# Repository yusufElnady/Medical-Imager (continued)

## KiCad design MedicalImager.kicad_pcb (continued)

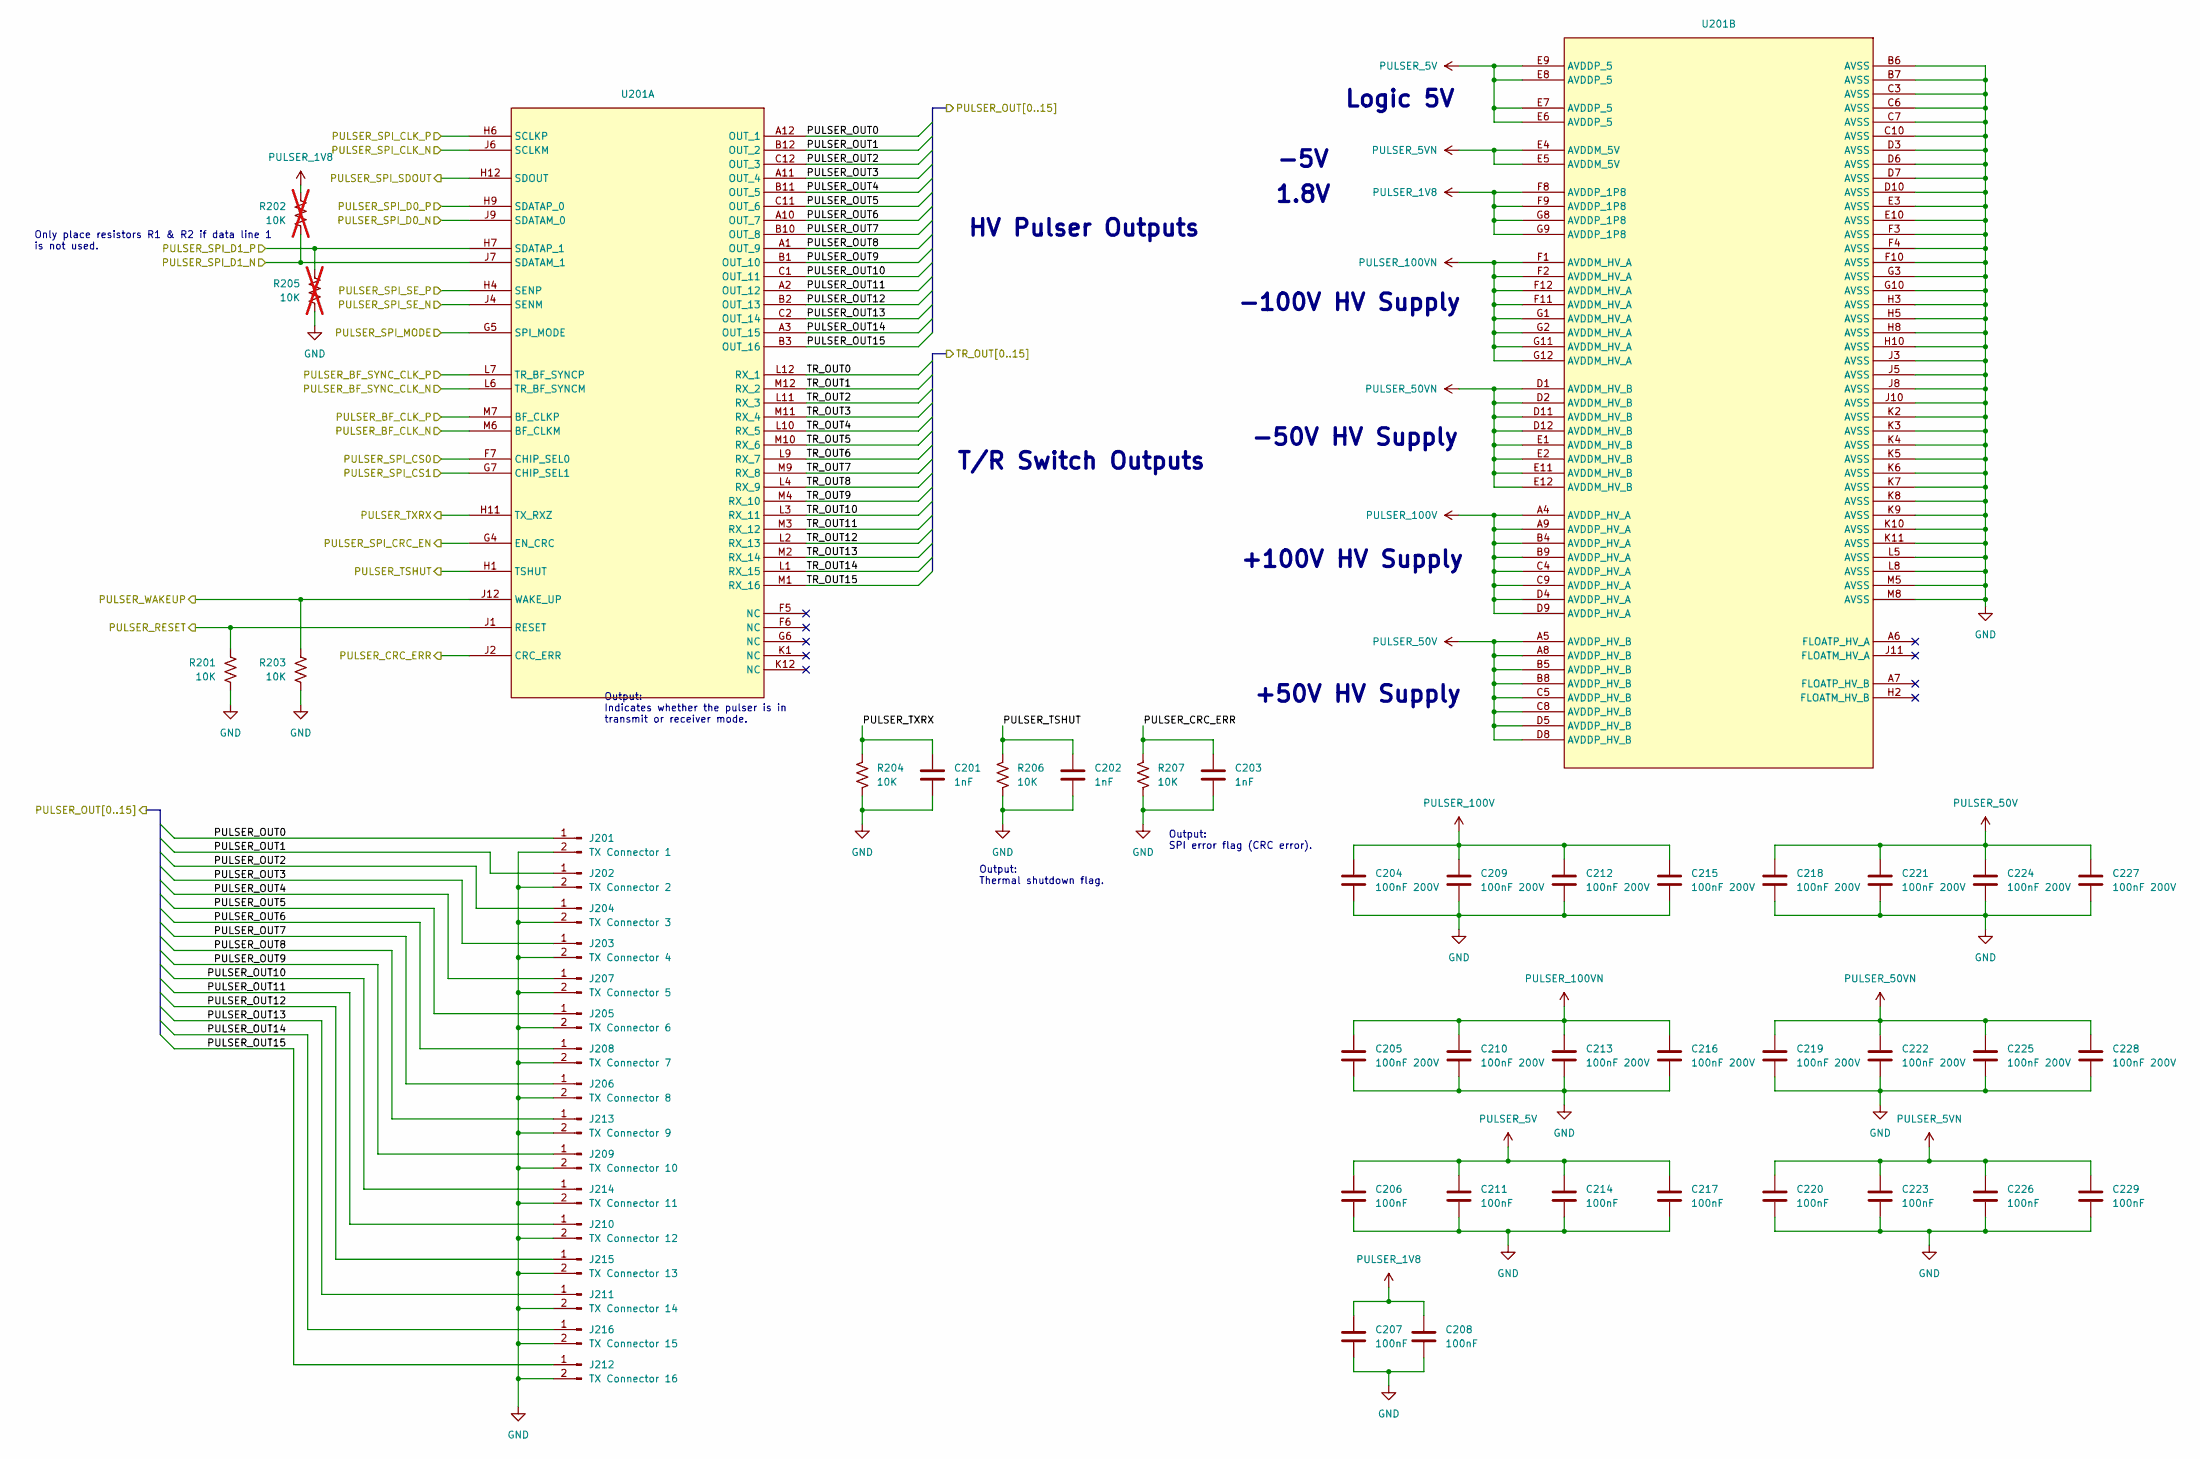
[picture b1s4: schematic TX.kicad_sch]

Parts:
C201, C202, C203: 1nF; C_0402_1005Metric
C204, C205, C209, C210, C212, C213, C215, C216, C218, C219, C221, C222, C224, C225, C227, C228: 100nF 200V; C_0805_2012Metric
C206, C207, C208, C211, C214, C217, C220, C223, C226, C229: 100nF; C_0402_1005Metric
J201: TX Connector 1; PinHeader_1x02_P2.54mm_Vertical
J202: TX Connector 2; PinHeader_1x02_P2.54mm_Vertical
J203: TX Connector 4; PinHeader_1x02_P2.54mm_Vertical
J204: TX Connector 3; PinHeader_1x02_P2.54mm_Vertical
J205: TX Connector 6; PinHeader_1x02_P2.54mm_Vertical
J206: TX Connector 8; PinHeader_1x02_P2.54mm_Vertical
J207: TX Connector 5; PinHeader_1x02_P2.54mm_Vertical
J208: TX Connector 7; PinHeader_1x02_P2.54mm_Vertical
J209: TX Connector 10; PinHeader_1x02_P2.54mm_Vertical
J210: TX Connector 12; PinHeader_1x02_P2.54mm_Vertical
J211: TX Connector 14; PinHeader_1x02_P2.54mm_Vertical
J212: TX Connector 16; PinHeader_1x02_P2.54mm_Vertical
J213: TX Connector 9; PinHeader_1x02_P2.54mm_Vertical
J214: TX Connector 11; PinHeader_1x02_P2.54mm_Vertical
J215: TX Connector 13; PinHeader_1x02_P2.54mm_Vertical
J216: TX Connector 15; PinHeader_1x02_P2.54mm_Vertical
R201, R203, R204, R206, R207: 10K; R_0402_1005Metric
R202, R205: 10K; R_0402_1005Metric; not fitted
U201: BGA-144_10.0x10.0mm_Layout12x12_P0.8mm_TI-ALH0144A

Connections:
/RX/TR_OUT0: U201.L12 (RX_1); also elsewhere on the board
/RX/TR_OUT1: U201.M12 (RX_2); also elsewhere on the board
/RX/TR_OUT2: U201.L11 (RX_3); also elsewhere on the board
/RX/TR_OUT3: U201.M11 (RX_4); also elsewhere on the board
/RX/TR_OUT4: U201.L10 (RX_5); also elsewhere on the board
/RX/TR_OUT5: U201.M10 (RX_6); also elsewhere on the board
/RX/TR_OUT6: U201.L9 (RX_7); also elsewhere on the board
/RX/TR_OUT7: U201.M9 (RX_8); also elsewhere on the board
/RX/TR_OUT8: U201.L4 (RX_9); also elsewhere on the board
/RX/TR_OUT9: U201.M4 (RX_10); also elsewhere on the board
/RX/TR_OUT10: U201.L3 (RX_11); also elsewhere on the board
/RX/TR_OUT11: U201.M3 (RX_12); also elsewhere on the board
/RX/TR_OUT12: U201.L2 (RX_13); also elsewhere on the board
/RX/TR_OUT13: U201.M2 (RX_14); also elsewhere on the board
/RX/TR_OUT14: U201.L1 (RX_15); also elsewhere on the board
/RX/TR_OUT15: U201.M1 (RX_16); also elsewhere on the board
/RX/TX_BF_CLK_N: U201.M6 (BF_CLKM); also elsewhere on the board
/RX/TX_BF_CLK_P: U201.M7 (BF_CLKP); also elsewhere on the board
/SOM/PULSER_BF_SYNC_CLK_N: U201.L6 (TR_BF_SYNCM); also elsewhere on the board
/SOM/PULSER_BF_SYNC_CLK_P: U201.L7 (TR_BF_SYNCP); also elsewhere on the board
/SOM/PULSER_RESET: R201.1, U201.J1 (RESET); also elsewhere on the board
/SOM/PULSER_SPI_CLK_N: U201.J6 (SCLKM); also elsewhere on the board
/SOM/PULSER_SPI_CLK_P: U201.H6 (SCLKP); also elsewhere on the board
/SOM/PULSER_SPI_CRC_EN: U201.G4 (EN_CRC); also elsewhere on the board
/SOM/PULSER_SPI_CS0: U201.F7 (CHIP_SEL0); also elsewhere on the board
/SOM/PULSER_SPI_CS1: U201.G7 (CHIP_SEL1); also elsewhere on the board
/SOM/PULSER_SPI_D0_N: U201.J9 (SDATAM_0); also elsewhere on the board
/SOM/PULSER_SPI_D0_P: U201.H9 (SDATAP_0); also elsewhere on the board
/SOM/PULSER_SPI_D1_N: R202.2, U201.J7 (SDATAM_1); also elsewhere on the board
/SOM/PULSER_SPI_D1_P: R205.1, U201.H7 (SDATAP_1); also elsewhere on the board
/SOM/PULSER_SPI_MODE: U201.G5 (SPI_MODE); also elsewhere on the board
/SOM/PULSER_SPI_SDOUT: U201.H12 (SDOUT); also elsewhere on the board
/SOM/PULSER_SPI_SE_N: U201.J4 (SENM); also elsewhere on the board
/SOM/PULSER_SPI_SE_P: U201.H4 (SENP); also elsewhere on the board
/SOM/PULSER_WAKEUP: R203.1, U201.J12 (WAKE_UP); also elsewhere on the board
/TX/PULSER_CRC_ERR: C203.1, R207.1, U201.J2 (CRC_ERR); also elsewhere on the board
/TX/PULSER_OUT0: J201.1, U201.A12 (OUT_1)
/TX/PULSER_OUT1: J202.1, U201.B12 (OUT_2)
/TX/PULSER_OUT2: J204.1, U201.C12 (OUT_3)
/TX/PULSER_OUT3: J203.1, U201.A11 (OUT_4)
/TX/PULSER_OUT4: J207.1, U201.B11 (OUT_5)
/TX/PULSER_OUT5: J205.1, U201.C11 (OUT_6)
/TX/PULSER_OUT6: J208.1, U201.A10 (OUT_7)
/TX/PULSER_OUT7: J206.1, U201.B10 (OUT_8)
/TX/PULSER_OUT8: J213.1, U201.A1 (OUT_9)
/TX/PULSER_OUT9: J209.1, U201.B1 (OUT_10)
/TX/PULSER_OUT10: J214.1, U201.C1 (OUT_11)
/TX/PULSER_OUT11: J210.1, U201.A2 (OUT_12)
/TX/PULSER_OUT12: J215.1, U201.B2 (OUT_13)
/TX/PULSER_OUT13: J211.1, U201.C2 (OUT_14)
/TX/PULSER_OUT14: J216.1, U201.A3 (OUT_15)
/TX/PULSER_OUT15: J212.1, U201.B3 (OUT_16)
/TX/PULSER_TSHUT: C202.1, R206.1, U201.H1 (TSHUT); also elsewhere on the board
/TX/PULSER_TXRX: C201.1, R204.1, U201.H11 (TX_RXZ); also elsewhere on the board
GND: C201.2, C202.2, C203.2, C204.2, C205.2, C206.2, C207.2, C208.2, C209.2, C210.2, C211.2, C212.2, C213.2, C214.2, C215.2, C216.2, C217.2, C218.2, C219.2, C220.2, C221.2, C222.2, C223.2, C224.2, C225.2, C226.2, C227.2, C228.2, C229.2, J201.2, J202.2, J203.2, J204.2, J205.2, J206.2, J207.2, J208.2, J209.2, J210.2, J211.2, J212.2, J213.2, J214.2, J215.2, J216.2, R201.2, R203.2, R204.2, R205.2, R206.2, R207.2, U201.B6 (AVSS), U201.B7 (AVSS), U201.C3 (AVSS), U201.C6 (AVSS), U201.C7 (AVSS), U201.C10 (AVSS), U201.D3 (AVSS), U201.D6 (AVSS), U201.D7 (AVSS), U201.D10 (AVSS), U201.E3 (AVSS), U201.E10 (AVSS), U201.F3 (AVSS), U201.F4 (AVSS), U201.F10 (AVSS), U201.G3 (AVSS), U201.G10 (AVSS), U201.H3 (AVSS), U201.H5 (AVSS), U201.H8 (AVSS), U201.H10 (AVSS), U201.J3 (AVSS), U201.J5 (AVSS), U201.J8 (AVSS), U201.J10 (AVSS), U201.K2 (AVSS), U201.K3 (AVSS), U201.K4 (AVSS), U201.K5 (AVSS), U201.K6 (AVSS), U201.K7 (AVSS), U201.K8 (AVSS), U201.K9 (AVSS), U201.K10 (AVSS), U201.K11 (AVSS), U201.L5 (AVSS), U201.L8 (AVSS), U201.M5 (AVSS), U201.M8 (AVSS); also elsewhere on the board
IM_5V: C206.1, C211.1, C214.1, C217.1, U201.E6 (AVDDP_5), U201.E7 (AVDDP_5), U201.E8 (AVDDP_5), U201.E9 (AVDDP_5); also elsewhere on the board
PULSER_1V8: C207.1, C208.1, R202.1, U201.F8 (AVDDP_1P8), U201.F9 (AVDDP_1P8), U201.G8 (AVDDP_1P8), U201.G9 (AVDDP_1P8); also elsewhere on the board
PULSER_5VN: C220.1, C223.1, C226.1, C229.1, U201.E4 (AVDDM_5V), U201.E5 (AVDDM_5V); also elsewhere on the board
PULSER_50V: C218.1, C221.1, C224.1, C227.1, U201.A5 (AVDDP_HV_B), U201.A8 (AVDDP_HV_B), U201.B5 (AVDDP_HV_B), U201.B8 (AVDDP_HV_B), U201.C5 (AVDDP_HV_B), U201.C8 (AVDDP_HV_B), U201.D5 (AVDDP_HV_B), U201.D8 (AVDDP_HV_B); also elsewhere on the board
PULSER_50VN: C219.1, C222.1, C225.1, C228.1, U201.D1 (AVDDM_HV_B), U201.D2 (AVDDM_HV_B), U201.D11 (AVDDM_HV_B), U201.D12 (AVDDM_HV_B), U201.E1 (AVDDM_HV_B), U201.E2 (AVDDM_HV_B), U201.E11 (AVDDM_HV_B), U201.E12 (AVDDM_HV_B); also elsewhere on the board
PULSER_100V: C204.1, C209.1, C212.1, C215.1, U201.A4 (AVDDP_HV_A), U201.A9 (AVDDP_HV_A), U201.B4 (AVDDP_HV_A), U201.B9 (AVDDP_HV_A), U201.C4 (AVDDP_HV_A), U201.C9 (AVDDP_HV_A), U201.D4 (AVDDP_HV_A), U201.D9 (AVDDP_HV_A); also elsewhere on the board
PULSER_100VN: C205.1, C210.1, C213.1, C216.1, U201.F1 (AVDDM_HV_A), U201.F2 (AVDDM_HV_A), U201.F11 (AVDDM_HV_A), U201.F12 (AVDDM_HV_A), U201.G1 (AVDDM_HV_A), U201.G2 (AVDDM_HV_A), U201.G11 (AVDDM_HV_A), U201.G12 (AVDDM_HV_A); also elsewhere on the board

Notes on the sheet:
-50V HV Supply
-5V
1.8V
+100V HV Supply
Logic 5V
HV Pulser Outputs
Only place resistors R1 & R2 if data line 1 is not used.
Output: Indicates whether the pulser is in transmit or receiver mode.
Output: SPI error flag (CRC error).
-100V HV Supply
+50V HV Supply
Output: Thermal shutdown flag.
T/R Switch Outputs

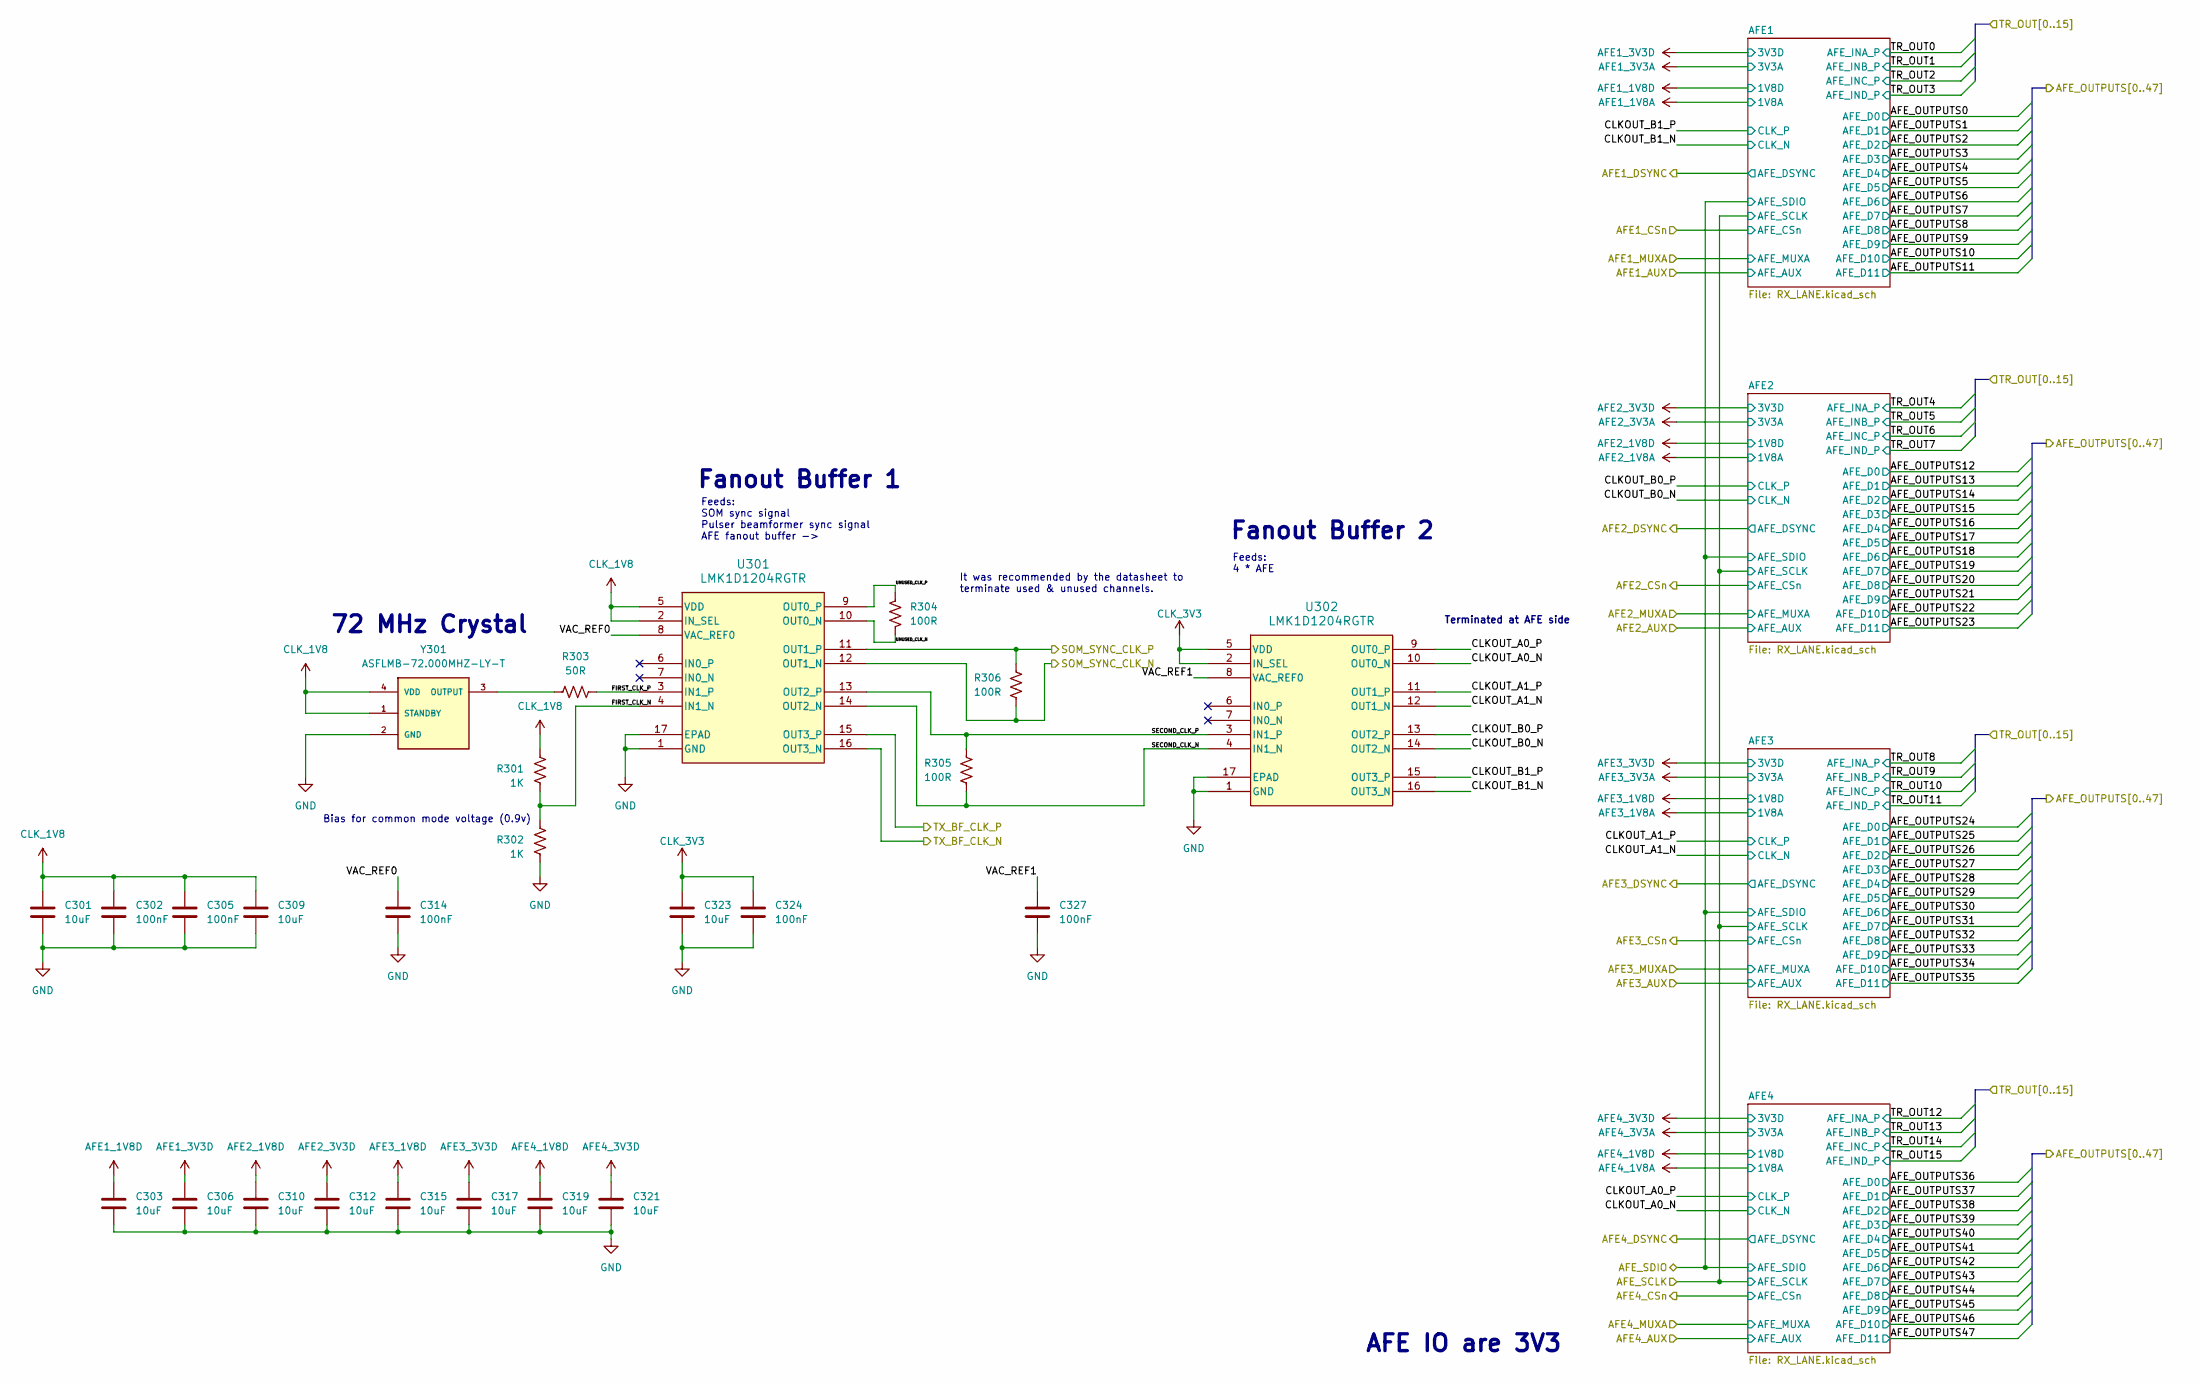
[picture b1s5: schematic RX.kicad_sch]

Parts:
C301, C303, C306, C309, C310, C312, C315, C317, C319, C321, C323: 10uF; C_0402_1005Metric
C302, C305, C314, C324, C327: 100nF; C_0402_1005Metric
R301, R302: 1K; R_0402_1005Metric
R303: 50R; R_0402_1005Metric
R304, R305, R306: 100R; R_0402_1005Metric
U301, U302: LMK1D1204RGTR; VQFN16_RGT_TEX
Y301: ASFLMB-72.000MHZ-LY-T; XTAL_ASFLMB-72.000MHZ-LY-T; PARTREV 1.4.2021

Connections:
/RX/CLKOUT_A0_N: U302.10 (OUT0_N); also elsewhere on the board
/RX/CLKOUT_A0_P: U302.9 (OUT0_P); also elsewhere on the board
/RX/CLKOUT_A1_N: U302.12 (OUT1_N); also elsewhere on the board
/RX/CLKOUT_A1_P: U302.11 (OUT1_P); also elsewhere on the board
/RX/CLKOUT_B0_N: U302.14 (OUT2_N); also elsewhere on the board
/RX/CLKOUT_B0_P: U302.13 (OUT2_P); also elsewhere on the board
/RX/CLKOUT_B1_N: U302.16 (OUT3_N); also elsewhere on the board
/RX/CLKOUT_B1_P: U302.15 (OUT3_P); also elsewhere on the board
/RX/FIRST_CLK_N: R301.2, R302.1, U301.4 (IN1_N)
/RX/FIRST_CLK_P: R303.1, U301.3 (IN1_P)
/RX/SECOND_CLK_N: R305.2, U301.14 (OUT2_N), U302.4 (IN1_N)
/RX/SECOND_CLK_P: R305.1, U301.13 (OUT2_P), U302.3 (IN1_P)
/RX/SOM_SYNC_CLK_N: R306.2, U301.12 (OUT1_N); also elsewhere on the board
/RX/SOM_SYNC_CLK_P: R306.1, U301.11 (OUT1_P); also elsewhere on the board
/RX/TX_BF_CLK_N: U301.16 (OUT3_N); also elsewhere on the board
/RX/TX_BF_CLK_P: U301.15 (OUT3_P); also elsewhere on the board
/RX/UNUSED_CLK_N: R304.2, U301.10 (OUT0_N)
/RX/UNUSED_CLK_P: R304.1, U301.9 (OUT0_P)
/RX/VAC_REF0: C314.2, U301.8 (VAC_REF0)
/RX/VAC_REF1: C327.2, U302.8 (VAC_REF0)
AFE1_1V8D: C303.1, C310.1; also elsewhere on the board
AFE1_3V3D: C306.1, C312.1; also elsewhere on the board
AFE3_1V8D: C315.1, C319.1; also elsewhere on the board
AFE3_3V3D: C317.1, C321.1; also elsewhere on the board
CLK_1V8: C301.2, C302.2, C305.2, C309.2, R301.1, U301.2 (IN_SEL), U301.5 (VDD), Y301.1 (STANDBY), Y301.4 (VDD); also elsewhere on the board
CLK_3V3: C323.2, C324.2, U302.2 (IN_SEL), U302.5 (VDD); also elsewhere on the board
GND: C301.1, C302.1, C303.2, C305.1, C306.2, C309.1, C310.2, C312.2, C314.1, C315.2, C317.2, C319.2, C321.2, C323.1, C324.1, C327.1, R302.2, U301.1 (GND), U301.17 (EPAD), U302.1 (GND), U302.17 (EPAD), Y301.2 (GND); also elsewhere on the board
unnamed: R303.2, Y301.3 (OUTPUT)

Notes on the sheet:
72 MHz Crystal
AFE IO are 3V3
Fanout Buffer 2
Fanout Buffer 1
Terminated at AFE side
It was recommended by the datasheet to terminate used & unused channels.
Feeds: SOM sync signal Pulser beamformer sync signal AFE fanout buffer ->
Bias for common mode voltage (0.9v)
Feeds: 4 * AFE

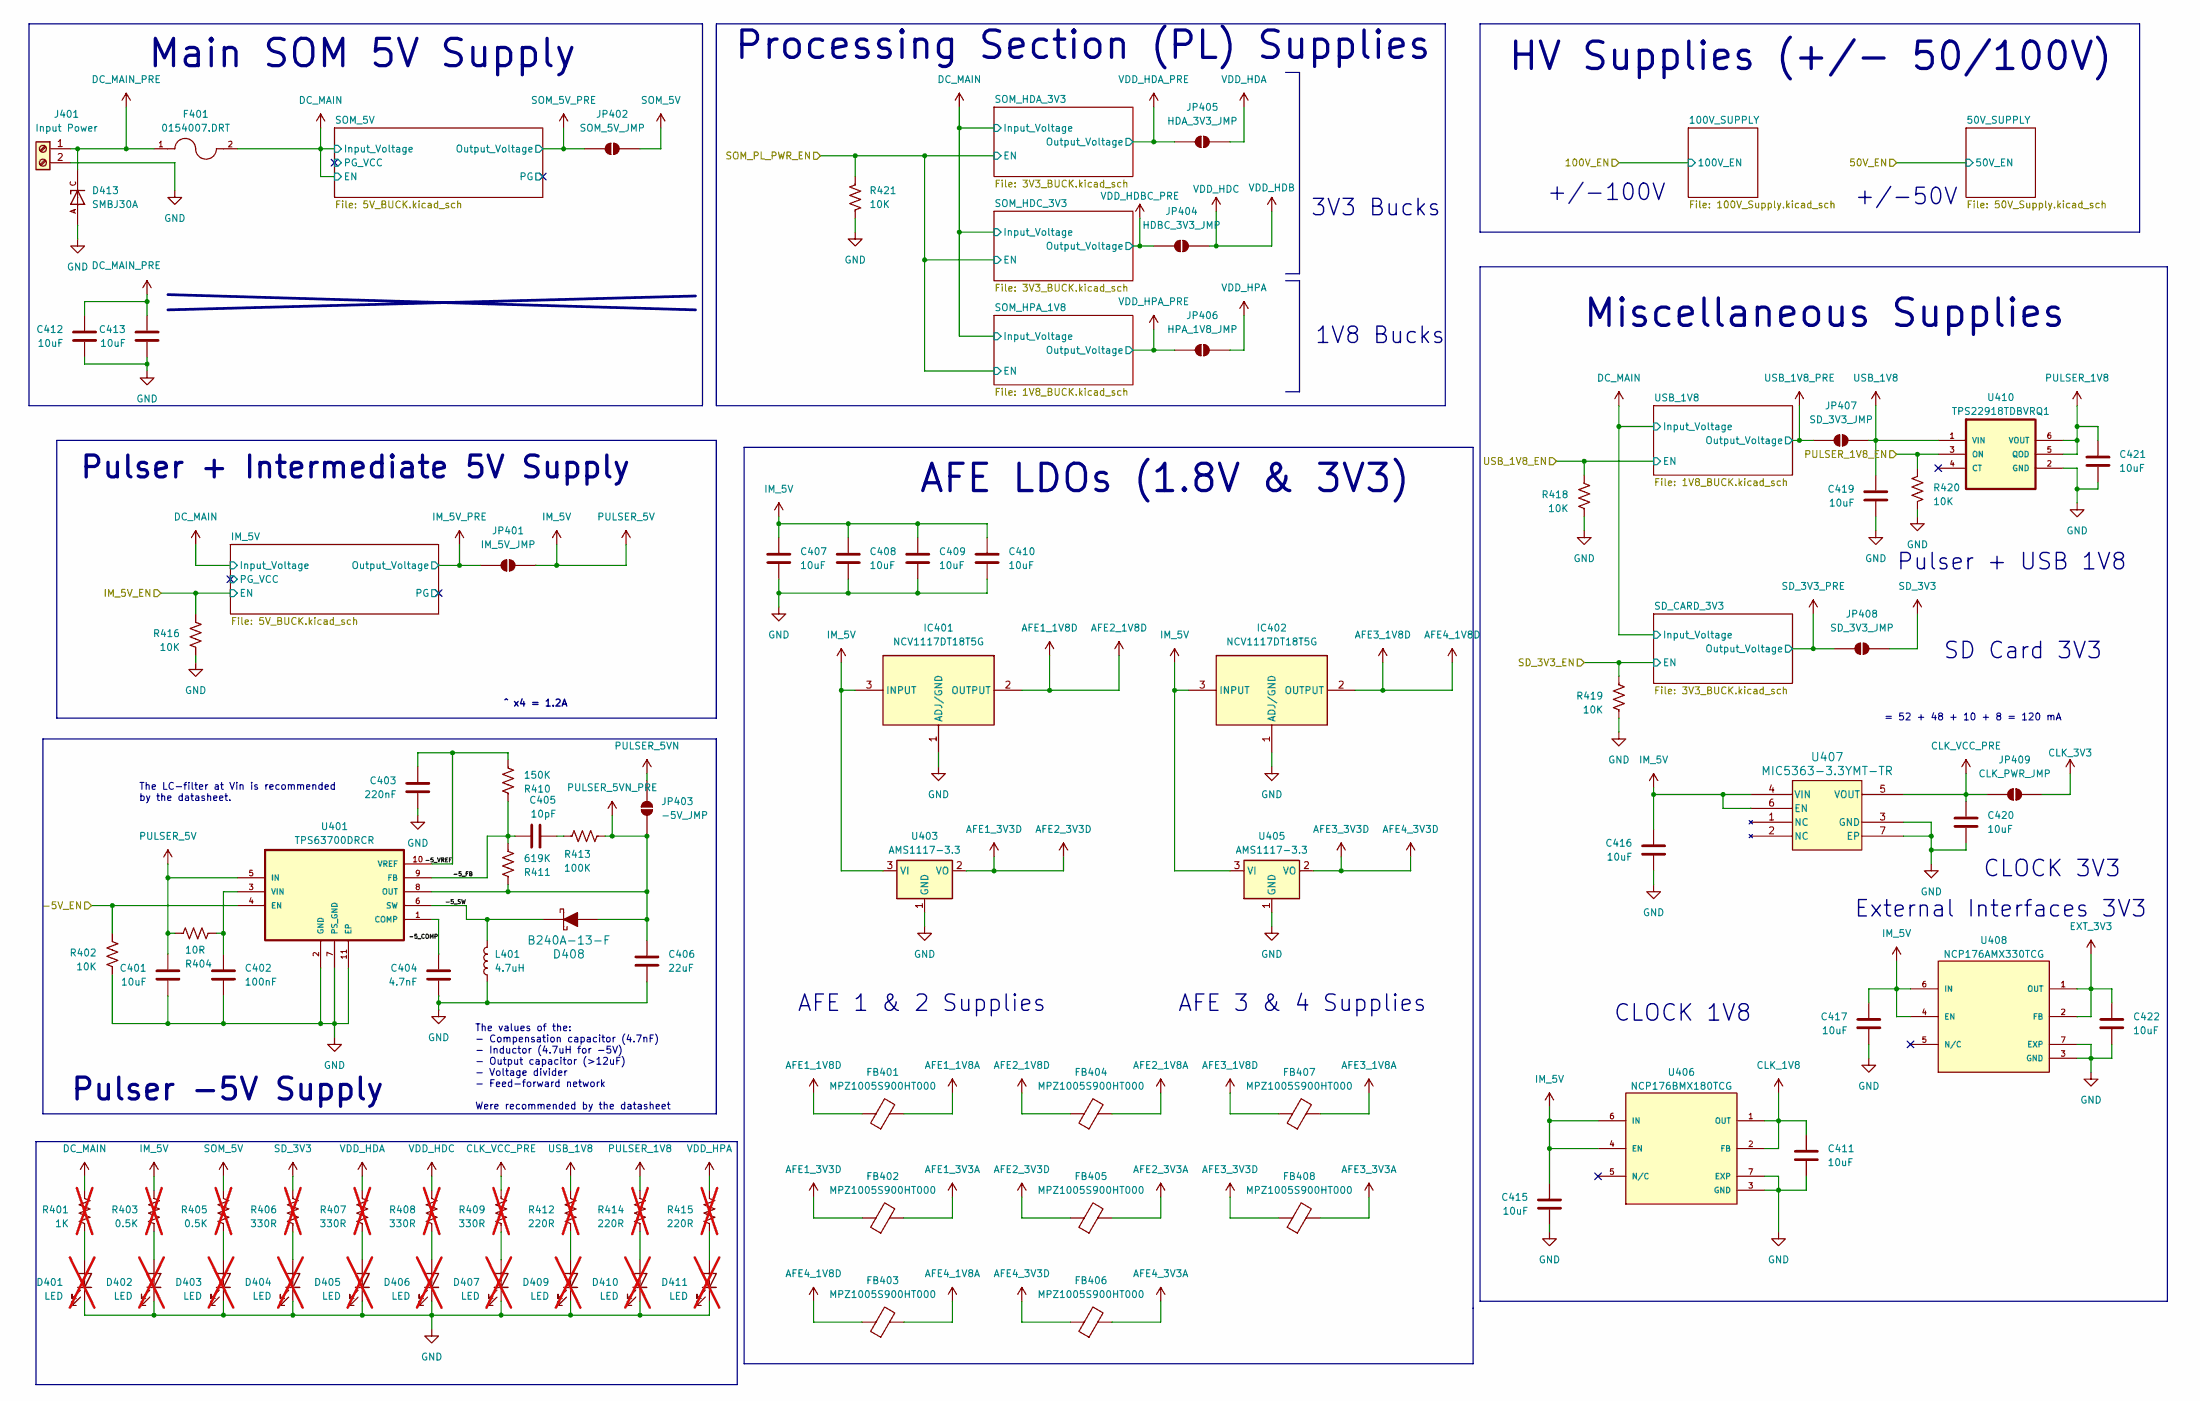
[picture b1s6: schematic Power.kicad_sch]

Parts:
C401, C412, C413: 10uF; C_0805_2012Metric
C402: 100nF; C_0402_1005Metric
C403: 220nF; C_0402_1005Metric
C404: 4.7nF; C_0603_1608Metric
C405: 10pF; C_0402_1005Metric
C406: 22uF; C_0805_2012Metric
C407, C408, C409, C410, C411, C415, C416, C417, C419, C420, C421, C422: 10uF; C_0402_1005Metric
D401, D402, D403, D404, D405, D406, D407, D409, D410, D411: LED; LED_0603_1608Metric; not fitted
D408: B240A-13-F; DO-214AC; MPN B240A-13-F; Digi-Key_PN B240A-FDICT-ND
D413: SMBJ30A; DIOM4336X265N; MPN SMBJ30A
F401: 0154007.DRT; FUSE_0154007.DRT; MPN 0154007.DRT
FB401, FB402, FB403, FB404, FB405, FB406, FB407, FB408: MPZ1005S900HT000; L_0402_1005Metric
IC401, IC402: NCV1117DT18T5G; NVD5117PLT4GVF01; Manufacturer_Part_Number NCV1117DT18T5G; Mouser Part Number 863-NCV1117DT18T5G
J401: Input Power; TerminalBlock_MaiXu_MX126-5.0-02P_1x02_P5.00mm
JP401: IM_5V_JMP; SolderJumper-2_P1.3mm_Open_TrianglePad1.0x1.5mm
JP402: SOM_5V_JMP; SolderJumper-2_P1.3mm_Open_TrianglePad1.0x1.5mm
JP403: -5V_JMP; SolderJumper-2_P1.3mm_Open_TrianglePad1.0x1.5mm
JP404: HDBC_3V3_JMP; SolderJumper-2_P1.3mm_Open_TrianglePad1.0x1.5mm
JP405: HDA_3V3_JMP; SolderJumper-2_P1.3mm_Open_TrianglePad1.0x1.5mm
JP406: HPA_1V8_JMP; SolderJumper-2_P1.3mm_Open_TrianglePad1.0x1.5mm
JP407, JP408: SD_3V3_JMP; SolderJumper-2_P1.3mm_Open_TrianglePad1.0x1.5mm
JP409: CLK_PWR_JMP; SolderJumper-2_P1.3mm_Open_TrianglePad1.0x1.5mm
L401: 4.7uH; L_0805_2012Metric
R401: 1K; R_0402_1005Metric; not fitted
R402, R416, R418, R419, R420, R421: 10K; R_0402_1005Metric
R403, R405: 0.5K; R_0402_1005Metric; not fitted
R404: 10R; R_0402_1005Metric
R406, R407, R408, R409: 330R; R_0402_1005Metric; not fitted
R410: 150K; R_0402_1005Metric
R411: 619K; R_0402_1005Metric
R412, R414, R415: 220R; R_0402_1005Metric; not fitted
R413: 100K; R_0402_1005Metric
U401: TPS63700DRCR; VREG_V62_16624-01YE
U403, U405: AMS1117-3.3; SOT-223-3_TabPin2
U406: NCP176BMX180TCG; PSON40P120X120X45-7N_NCP176BMX180TCG; PARTREV 5
U407: MIC5363-3.3YMT-TR; TMLF-6_MT_MCH
U408: NCP176AMX330TCG; PSON40P120X120X45-7N_NCP176AMX330TCG; PARTREV 5
U410: TPS22918TDBVRQ1; SOT95P280X145-6N

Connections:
/Power/-5V_EN: R402.1, U401.4 (EN); also elsewhere on the board
/Power/-5_COMP: C404.1, U401.1 (COMP)
/Power/-5_FB: C405.1, R410.1, R411.2, U401.9 (FB)
/Power/-5_SW: D408.K, L401.2, U401.6 (SW)
/Power/-5_VREF: C403.1, R410.2, U401.10 (VREF)
/Power/IM_5V_EN: R416.1; also elsewhere on the board
/Power/PULSER_1V8_EN: R420.1, U410.3 (ON); also elsewhere on the board
/Power/SD_3V3_EN: R419.1; also elsewhere on the board
/Power/SOM_PL_PWR_EN: R421.1; also elsewhere on the board
/Power/USB_1V8_EN: R418.1; also elsewhere on the board
AFE1_1V8A: FB401.2; also elsewhere on the board
AFE1_1V8D: FB401.1, FB404.1, IC401.2 (OUTPUT); also elsewhere on the board
AFE1_3V3A: FB402.2; also elsewhere on the board
AFE1_3V3D: FB402.1, FB405.1, U403.2 (VO); also elsewhere on the board
AFE2_1V8A: FB404.2; also elsewhere on the board
AFE2_3V3A: FB405.2; also elsewhere on the board
AFE3_1V8A: FB407.2; also elsewhere on the board
AFE3_1V8D: FB403.1, FB407.1, IC402.2 (OUTPUT); also elsewhere on the board
AFE3_3V3A: FB408.2; also elsewhere on the board
AFE3_3V3D: FB406.1, FB408.1, U405.2 (VO); also elsewhere on the board
AFE4_1V8A: FB403.2; also elsewhere on the board
AFE4_3V3A: FB406.2; also elsewhere on the board
CLK_1V8: C411.1, U406.1 (OUT), U406.2 (FB); also elsewhere on the board
CLK_3V3: JP409.2 (B); also elsewhere on the board
CLK_VCC_PRE: C420.1, JP409.1 (A), R409.1, U407.5 (VOUT)
DC_MAIN: F401.2, R401.1; also elsewhere on the board
DC_MAIN_PRE: C412.1, C413.1, D413.1 (K), D413.C, F401.1, J401.1; also elsewhere on the board
EXT_3V3: C422.1, U408.1 (OUT), U408.2 (FB); also elsewhere on the board
GND: C401.2, C402.2, C403.2, C404.2, C406.2, C407.2, C408.2, C409.2, C410.2, C411.2, C412.2, C413.2, C415.2, C416.2, C417.2, C419.2, C420.2, C421.2, C422.2, D401.1 (K), D402.1 (K), D403.1 (K), D404.1 (K), D405.1 (K), D406.1 (K), D407.1 (K), D409.1 (K), D410.1 (K), D411.1 (K), D413.2 (A), D413.A, IC401.1 (ADJ/GND), IC402.1 (ADJ/GND), J401.2, L401.1, R402.2, R416.2, R418.2, R419.2, R420.2, R421.2, U401.2 (GND), U401.7 (PS_GND), U401.11 (EP), U403.1 (GND), U405.1 (GND), U406.3 (GND), U406.7 (EXP), U407.3 (GND), U407.7 (EP), U408.3 (GND), U408.7 (EXP), U410.2 (GND); also elsewhere on the board
IM_5V: C401.1, C407.1, C408.1, C409.1, C410.1, C415.1, C416.1, C417.1, IC401.3 (INPUT), IC402.3 (INPUT), JP401.2 (B), R403.1, R404.1, U401.5 (IN), U403.3 (VI), U405.3 (VI), U406.4 (EN), U406.6 (IN), U407.4 (VIN), U407.6 (EN), U408.4 (EN), U408.6 (IN); also elsewhere on the board
IM_5V_PRE: JP401.1 (A); also elsewhere on the board
unnamed: C405.2, R413.1
unnamed: D401.2 (A), R401.2
unnamed: D402.2 (A), R403.2
unnamed: D403.2 (A), R405.2
unnamed: D404.2 (A), R406.2
unnamed: D405.2 (A), R407.2
unnamed: D406.2 (A), R408.2
unnamed: D407.2 (A), R409.2
unnamed: D409.2 (A), R412.2
unnamed: D410.2 (A), R414.2
unnamed: D411.2 (A), R415.2
unnamed: C402.1, R404.2, U401.3 (VIN)
PULSER_1V8: C421.1, R414.1, U410.5 (QOD), U410.6 (VOUT); also elsewhere on the board
PULSER_5VN: JP403.2 (B); also elsewhere on the board
PULSER_5VN_PRE: C406.1, D408.A, JP403.1 (A), R411.1, R413.2, U401.8 (OUT)
SD_3V3: JP408.2 (B), R406.1; also elsewhere on the board
SD_3V3_PRE: JP408.1 (A); also elsewhere on the board
SOM_5V: JP402.2 (B), R405.1; also elsewhere on the board
SOM_5V_PRE: JP402.1 (A); also elsewhere on the board
USB_1V8: C419.1, JP407.2 (B), R412.1, U410.1 (VIN); also elsewhere on the board
USB_1V8_PRE: JP407.1 (A); also elsewhere on the board
VDD_HDA: JP405.2 (B), R407.1; also elsewhere on the board
VDD_HDA_PRE: JP405.1 (A); also elsewhere on the board
VDD_HDB: JP404.2 (B), R408.1; also elsewhere on the board
VDD_HDBC_PRE: JP404.1 (A); also elsewhere on the board
VDD_HPA: JP406.2 (B), R415.1; also elsewhere on the board
VDD_HPA_PRE: JP406.1 (A); also elsewhere on the board

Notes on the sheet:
AFE 1 & 2 Supplies
+/-100V
^ x4 = 1.2A
= 52 + 48 + 10 + 8 = 120 mA
HV Supplies (+/- 50/100V)
Main SOM 5V Supply
+/-50V
Pulser -5V Supply
CLOCK 3V3
1V8 Bucks
Processing Section (PL) Supplies
SD Card 3V3
The values of the: - Compensation capacitor (4.7nF) - Inductor (4.7uH for -5V) - Output capacitor (>12uF) - Voltage divider - Feed-forward network Were recommended by the datasheet
Pulser + USB 1V8
CLOCK 1V8
Miscellaneous Supplies
3V3 Bucks
External Interfaces 3V3
AFE LDOs (1.8V & 3V3)
The LC-filter at Vin is recommended by the datasheet.
Pulser + Intermediate 5V Supply
AFE 3 & 4 Supplies
